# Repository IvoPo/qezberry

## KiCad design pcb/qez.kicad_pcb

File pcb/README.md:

# QEZBerry PCB

### Features

- Powered by an rp2040
- Basic ESD and overvoltage protection
- Centered USB type-C port for a detachable cable
- Multiple layout options (see below)
- Fully programmable using [QMK](https://qmk.fm) and [Vial](https://get.vial.today)

---

### Supported layouts

---

### Preview

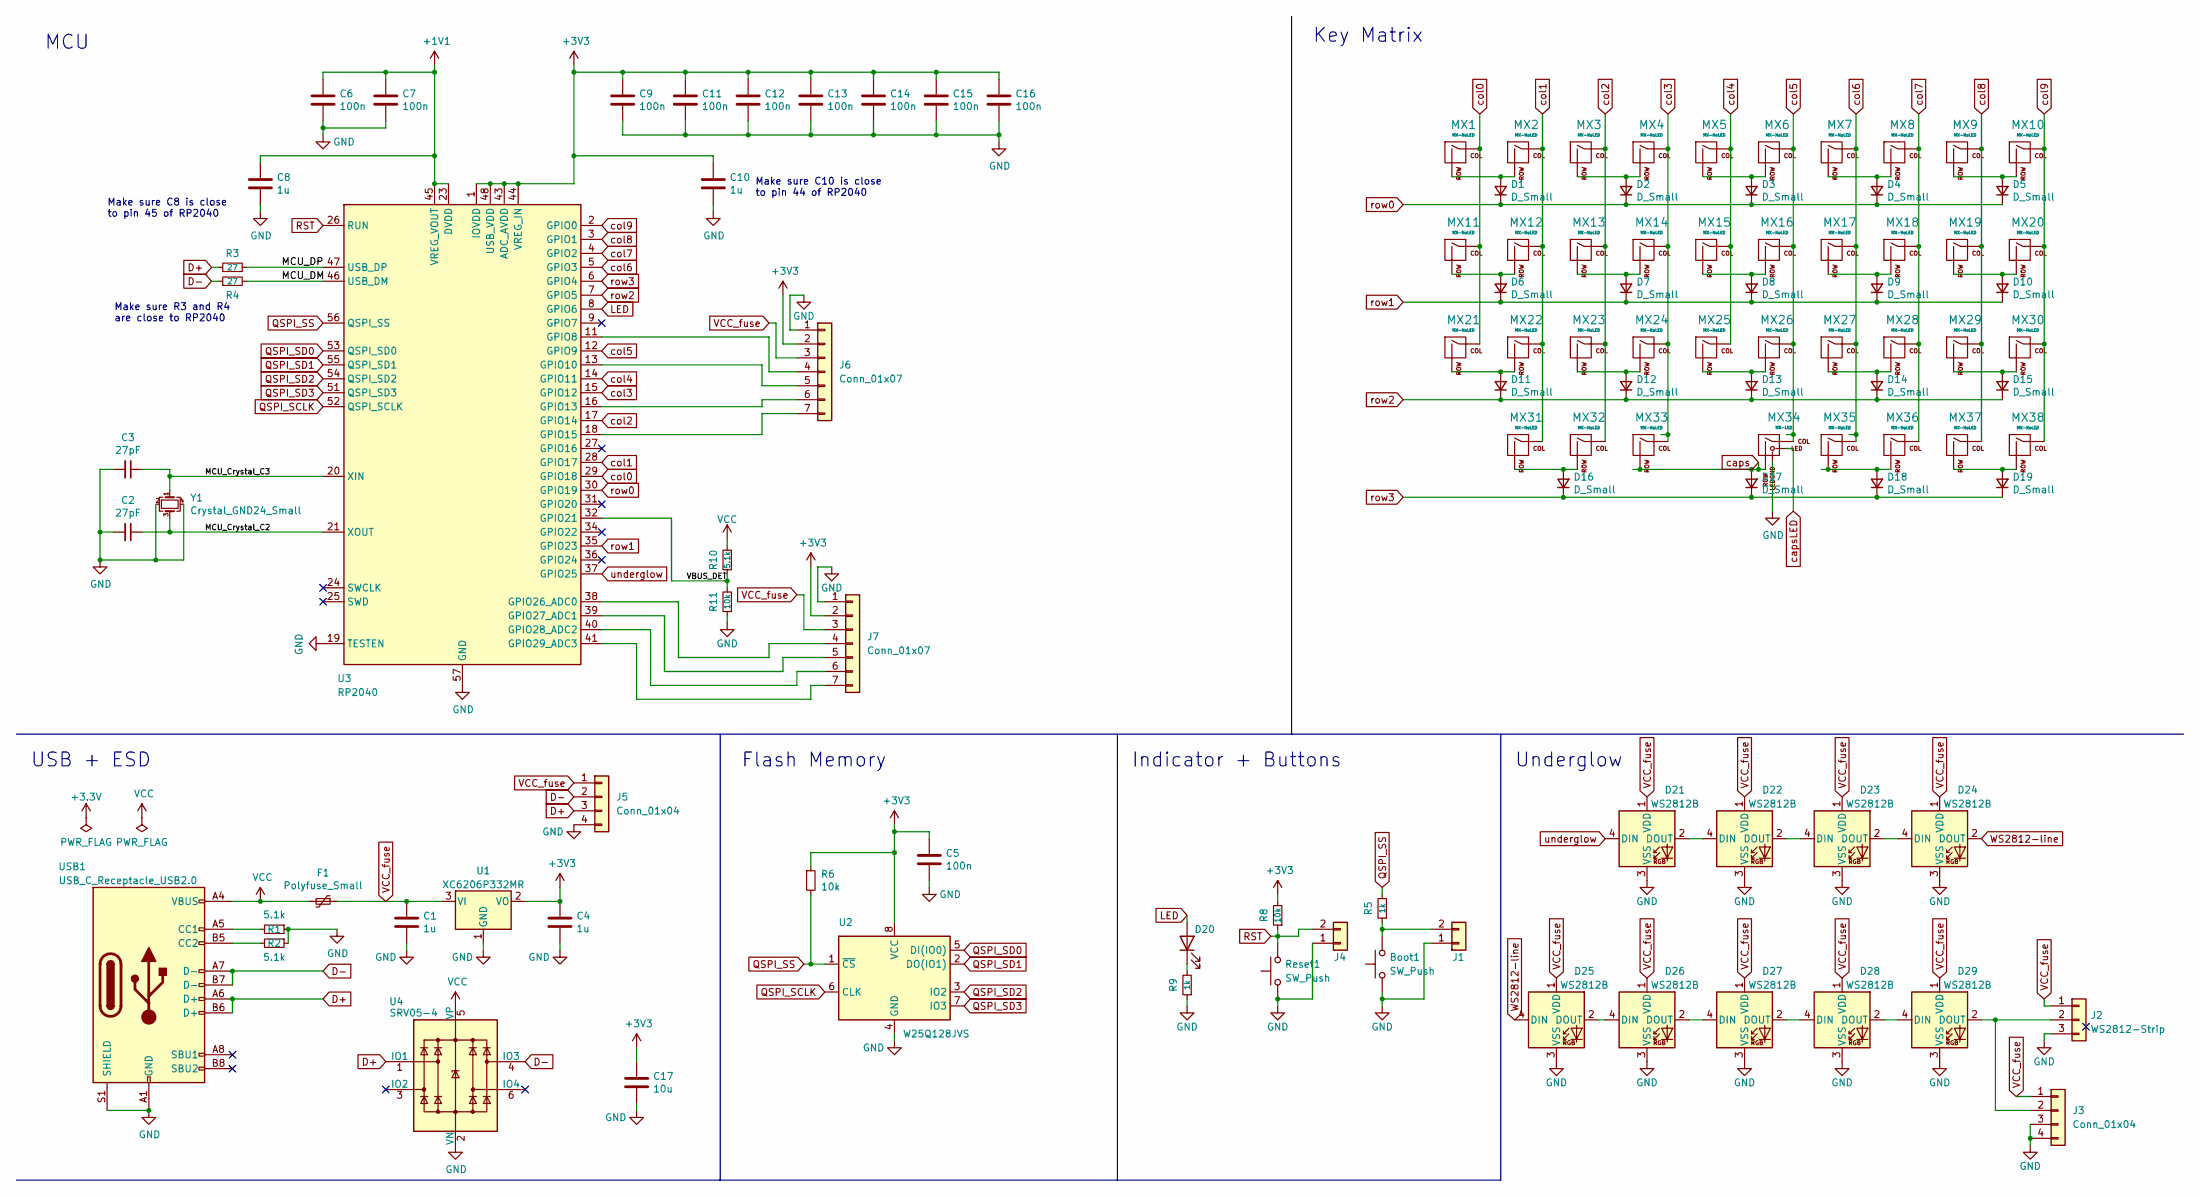
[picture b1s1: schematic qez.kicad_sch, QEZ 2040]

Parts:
Boot1: SW_Push; SW_SPST_SKQG_WithStem; LCSC C319433
C1, C4, C8, C10: 1u; C_0402_1005Metric; LCSC C1523
C2, C3: 27pF; C_0402_1005Metric; LCSC C1557
C5, C6, C7, C9, C11, C12, C13, C14, C15, C16: 100n; C_0402_1005Metric; LCSC C307331
C17: 10u; C_0805_2012Metric; LCSC C1710
D1, D2, D3, D4, D5, D6, D7, D8, D9, D10, D11, D12, D13, D14, D15, D16, D17, D18, D19: D_Small; D_SOT-23_ANK; LCSC C68978
D20: LED; LED_0402_1005Metric; LCSC C130719
D21, D22, D23, D24, D25, D26, D27, D28, D29: WS2812B; LED_WS2812B_PLCC4_5.0x5.0mm_P3.2mm
F1: Polyfuse_Small; Fuse_1206_3216Metric; LCSC C69688
J1, J4: Conn_01x02; PinHeader_1x02_P1.27mm_Vertical
J2: WS2812-Strip; PinHeader_1x03_P1.27mm_Vertical
J3: Conn_01x04; Molex_Pico-EZmate_78171-0004_1x04-1MP_P1.20mm_Vertical
J5: Conn_01x04
J6: Conn_01x07; PinSocket_1x07_P2.00mm_Vertical
J7: Conn_01x07; PinSocket_1x07_P1.27mm_Vertical
MX1, MX2, MX3, MX4, MX5, MX6, MX7, MX8, MX9, MX12, MX13, MX14, MX15, MX16, MX17, MX18, MX19, MX20, MX22, MX23, MX24, MX25, MX26, MX27, MX28, MX29, MX31, MX32, MX36, MX37, MX38: MX-NoLED; MXOnly-1U-NoLED
MX10, MX11: MX-NoLED; MXOnly-1.25U-NoLED
MX21: MX-NoLED; MXOnly-1.75U-NoLED
MX30: MX-NoLED; MXOnly-1.5U-NoLED
MX33: MX-NoLED; MXOnly-2.75U-ReversedStabilizers-NoLED
MX34: MX-LED; MXOnly-1.25U
MX35: MX-NoLED; MXOnly-2.25U-ReversedStabilizers-NoLED
R1, R2: 5.1k; R_0805_2012Metric; LCSC C27834
R3, R4: 27; R_0402_1005Metric; LCSC C17561
R5, R9: 1k; R_0402_1005Metric; LCSC C11702
R6: 10k; R_0805_2012Metric; LCSC C17414
R8, R11: 10k; R_0402_1005Metric; LCSC C25744
R10: 5.1k; R_0402_1005Metric; LCSC C25905
Reset1: SW_Push; SW_SPST_SKQG_WithStem; LCSC C319433
U1: XC6206P332MR; SOT-23; LCSC C5446
U2: W25Q128JVS; SOIC-8_5.23x5.23mm_P1.27mm; LCSC C97521
U3: RP2040; QFN-56-1EP_7x7mm_P0.4mm_EP3.2x3.2mm; LCSC C2040
U4: SRV05-4; SOT-23-6; LCSC C85364
USB1: USB_C_Receptacle_USB2.0; USB_C_Receptacle_HRO_TYPE-C-31-M-12; LCSC C165948
Y1: Crystal_GND24_Small; Crystal_SMD_3225-4Pin_3.2x2.5mm; LCSC C13738

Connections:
+1V1: C6.1, C7.1, C8.1, U3.23 (DVDD), U3.45 (VREG_VOUT), U3.50 (DVDD)
+3V3: C4.1, C5.1, C9.1, C10.1, C11.1, C12.1, C13.1, C14.1, C15.1, C16.1, C17.1, J6.2, J7.2, R6.1, R8.2, U1.2 (VO), U2.8 (VCC), U3.1 (IOVDD), U3.10 (IOVDD), U3.22 (IOVDD), U3.33 (IOVDD), U3.42 (IOVDD), U3.43 (ADC_AVDD), U3.44 (VREG_IN), U3.48 (USB_VDD), U3.49 (IOVDD)
/MCU_Crystal_C2: C2.1, U3.21 (XOUT), Y1.3
/MCU_Crystal_C3: C3.1, U3.20 (XIN), Y1.1
/MCU_DM: R4.2, U3.46 (USB_DM)
/MCU_DP: R3.2, U3.47 (USB_DP)
/VBUS_DET: R10.1, R11.2, U3.32 (GPIO21)
D+: J5.3, R3.1, U4.1 (IO1), USB1.A6 (D+), USB1.B6 (D+)
D-: J5.2, R4.1, U4.4 (IO3), USB1.A7 (D-), USB1.B7 (D-)
GND: Boot1.1, C1.2, C2.2, C3.2, C4.2, C5.2, C6.2, C7.2, C8.2, C9.2, C10.2, C11.2, C12.2, C13.2, C14.2, C15.2, C16.2, C17.2, D21.3 (VSS), D22.3 (VSS), D23.3 (VSS), D24.3 (VSS), D25.3 (VSS), D26.3 (VSS), D27.3 (VSS), D28.3 (VSS), D29.3 (VSS), J1.1, J2.3, J3.3, J3.4, J4.1, J5.4, J6.1, J7.1, MX34.4 (LEDGND), R1.1, R2.1, R9.1, R11.1, Reset1.1, U1.1 (GND), U2.4 (GND), U3.19 (TESTEN), U3.57 (GND), U4.2 (VN), USB1.A1 (GND), USB1.A12 (GND), USB1.B1 (GND), USB1.B12 (GND), USB1.S1 (SHIELD), Y1.2, Y1.4
LED: D20.2 (A), U3.8 (GPIO6)
unnamed: D1.2 (A), MX1.2 (ROW), MX2.2 (ROW)
unnamed: D2.2 (A), MX3.2 (ROW), MX4.2 (ROW)
unnamed: D3.2 (A), MX5.2 (ROW), MX6.2 (ROW)
unnamed: D4.2 (A), MX7.2 (ROW), MX8.2 (ROW)
unnamed: D5.2 (A), MX9.2 (ROW), MX10.2 (ROW)
unnamed: D6.2 (A), MX11.2 (ROW), MX12.2 (ROW)
unnamed: D7.2 (A), MX13.2 (ROW), MX14.2 (ROW)
unnamed: D8.2 (A), MX15.2 (ROW), MX16.2 (ROW)
unnamed: D9.2 (A), MX17.2 (ROW), MX18.2 (ROW)
unnamed: D10.2 (A), MX19.2 (ROW), MX20.2 (ROW)
unnamed: D11.2 (A), MX21.2 (ROW), MX22.2 (ROW)
unnamed: D12.2 (A), MX23.2 (ROW), MX24.2 (ROW)
unnamed: D13.2 (A), MX25.2 (ROW), MX26.2 (ROW)
unnamed: D14.2 (A), MX27.2 (ROW), MX28.2 (ROW)
unnamed: D15.2 (A), MX29.2 (ROW), MX30.2 (ROW)
unnamed: D16.2 (A), MX31.2 (ROW), MX32.2 (ROW)
unnamed 28: D18.2 (A), MX35.2 (ROW), MX36.2 (ROW); also elsewhere on the board
unnamed: D19.2 (A), MX37.2 (ROW), MX38.2 (ROW)
unnamed: D20.1 (K), R9.2
unnamed: D21.2 (DOUT), D22.4 (DIN)
unnamed: D22.2 (DOUT), D23.4 (DIN)
unnamed: D23.2 (DOUT), D24.4 (DIN)
unnamed: D25.2 (DOUT), D26.4 (DIN)
unnamed: D26.2 (DOUT), D27.4 (DIN)
unnamed: D27.2 (DOUT), D28.4 (DIN)
unnamed: D28.2 (DOUT), D29.4 (DIN)
unnamed: D29.2 (DOUT), J2.2, J3.2
unnamed: Boot1.2, J1.2, R5.1
unnamed: J6.4, U3.11 (GPIO8)
unnamed: J6.5, U3.13 (GPIO10)
unnamed: J6.6, U3.16 (GPIO13)
unnamed: J6.7, U3.18 (GPIO15)
unnamed: J7.4, U3.38 (GPIO26_ADC0)
unnamed: J7.5, U3.39 (GPIO27_ADC1)
unnamed: J7.6, U3.40 (GPIO28_ADC2)
unnamed: J7.7, U3.41 (GPIO29_ADC3)
unnamed: R1.2, USB1.A5 (CC1)
unnamed: R2.2, USB1.B5 (CC2)
QSPI_SCLK: U2.6 (CLK), U3.52 (QSPI_SCLK)
QSPI_SD0: U2.5 (DI(IO0)), U3.53 (QSPI_SD0)
QSPI_SD1: U2.2 (DO(IO1)), U3.55 (QSPI_SD1)
QSPI_SD2: U2.3 (IO2), U3.54 (QSPI_SD2)
QSPI_SD3: U2.7 (IO3), U3.51 (QSPI_SD3)
QSPI_SS: R5.2, R6.2, U2.1 (~CS), U3.56 (QSPI_SS)
RST: J4.2, R8.1, Reset1.2, U3.26 (RUN)
VCC: F1.2, R10.2, U4.5 (VP), USB1.A4 (VBUS), USB1.A9 (VBUS), USB1.B4 (VBUS), USB1.B9 (VBUS)
VCC_fuse: C1.1, D21.1 (VDD), D22.1 (VDD), D23.1 (VDD), D24.1 (VDD), D25.1 (VDD), D26.1 (VDD), D27.1 (VDD), D28.1 (VDD), D29.1 (VDD), F1.1, J2.1, J3.1, J5.1, J6.3, J7.3, U1.3 (VI)
WS2812-line: D24.2 (DOUT), D25.4 (DIN)
caps: D17.2 (A), MX33.2 (ROW), MX34.2 (ROW)
col0: MX1.1 (COL), MX11.1 (COL), MX21.1 (COL), U3.29 (GPIO18)
col1: MX2.1 (COL), MX12.1 (COL), MX22.1 (COL), MX31.1 (COL), U3.28 (GPIO17)
col2: MX3.1 (COL), MX13.1 (COL), MX23.1 (COL), MX32.1 (COL), U3.17 (GPIO14)
col3: MX4.1 (COL), MX14.1 (COL), MX24.1 (COL), MX33.1 (COL), U3.15 (GPIO12); also elsewhere on the board
col4: MX5.1 (COL), MX15.1 (COL), MX25.1 (COL), U3.14 (GPIO11)
col5: MX6.1 (COL), MX16.1 (COL), MX26.1 (COL), MX34.1 (COL), U3.12 (GPIO9); also elsewhere on the board
col6: MX7.1 (COL), MX17.1 (COL), MX27.1 (COL), MX35.1 (COL), U3.5 (GPIO3); also elsewhere on the board
col7: MX8.1 (COL), MX18.1 (COL), MX28.1 (COL), MX36.1 (COL), U3.4 (GPIO2)
col8: MX9.1 (COL), MX19.1 (COL), MX29.1 (COL), MX37.1 (COL), U3.3 (GPIO1)
col9: MX10.1 (COL), MX20.1 (COL), MX30.1 (COL), MX38.1 (COL), U3.2 (GPIO0)
row0: D1.1 (K), D2.1 (K), D3.1 (K), D4.1 (K), D5.1 (K), U3.30 (GPIO19)
row1: D6.1 (K), D7.1 (K), D8.1 (K), D9.1 (K), D10.1 (K), U3.35 (GPIO23)
row2: D11.1 (K), D12.1 (K), D13.1 (K), D14.1 (K), D15.1 (K), U3.7 (GPIO5)
row3: D16.1 (K), D17.1 (K), D18.1 (K), D19.1 (K), U3.6 (GPIO4)
underglow: D21.4 (DIN), U3.37 (GPIO25)

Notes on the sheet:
Key Matrix
USB + ESD
Make sure C10 is close to pin 44 of RP2040
Make sure R3 and R4 are close to RP2040
Make sure C8 is close to pin 45 of RP2040
Underglow
MCU
Flash Memory
Indicator + Buttons

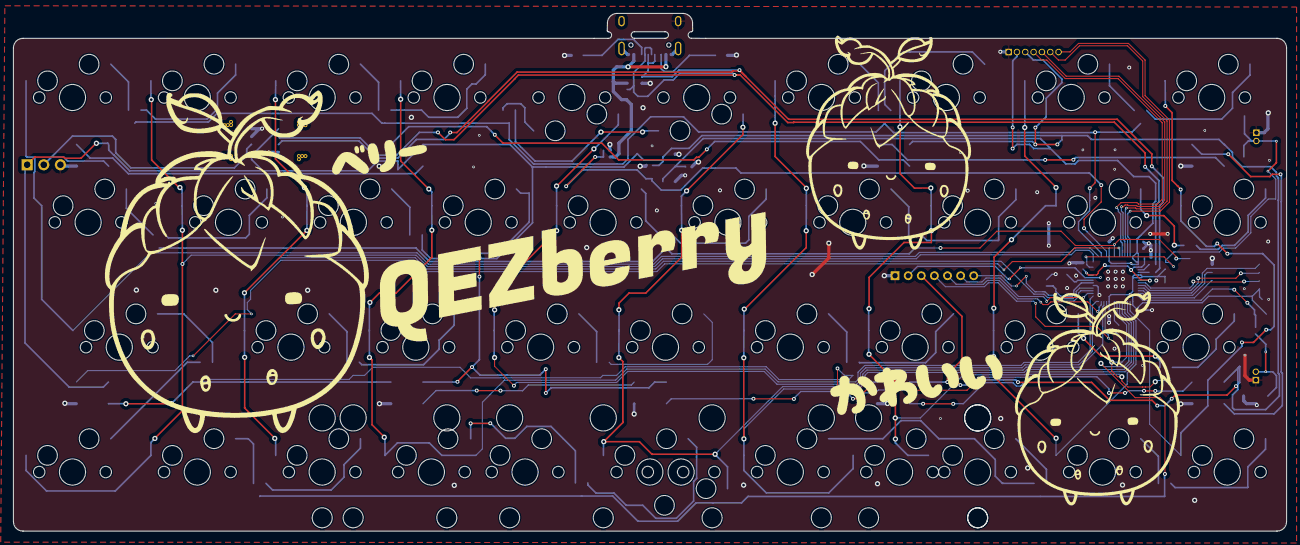
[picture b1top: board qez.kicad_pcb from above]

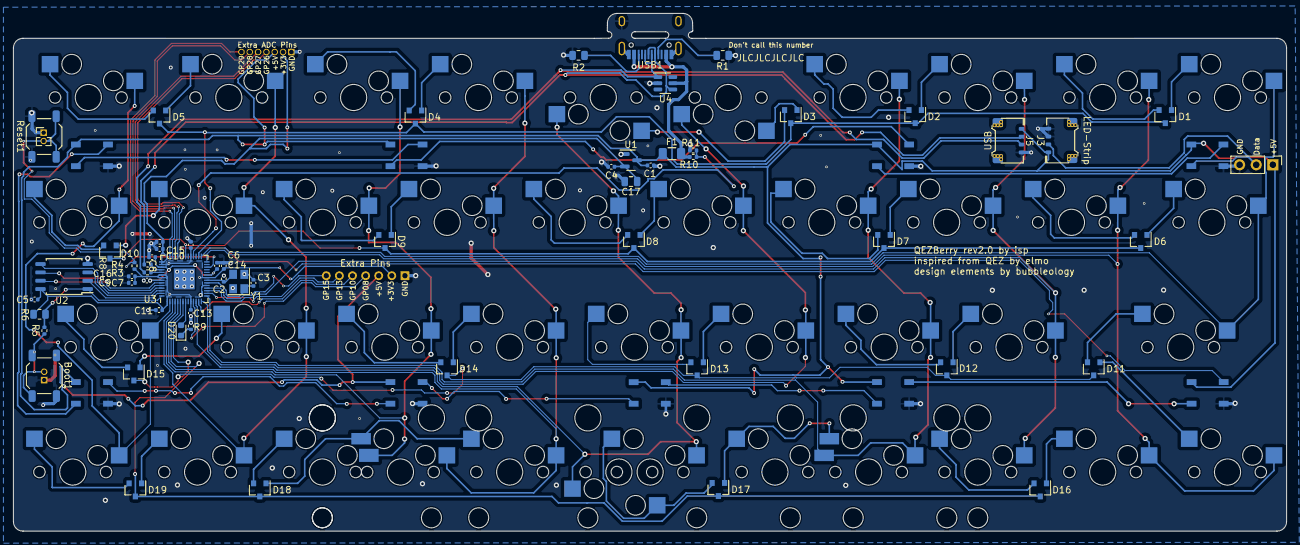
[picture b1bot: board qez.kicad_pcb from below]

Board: 2 copper layers, 194.3 x 79.0 mm, 113 parts (72 on the bottom side), 76 nets.

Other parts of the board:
MX39: MX-NoLED; MXOnly-2.25U-Hotswap-ReversedStabilizers
MX40: MX-NoLED; MXOnly-2U-Hotswap-ReversedStabilizers
MX41: MX-LED; MXOnly-6.25U-Hotswap-ReversedStabilizers-LED

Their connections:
unnamed: MX39.2 (ROW), MX41.2 (ROW)
unnamed 28: MX40.2 (ROW); also elsewhere on the board
col3: MX39.1 (COL); also elsewhere on the board
col5: MX41.1 (COL); also elsewhere on the board
col6: MX40.1 (COL); also elsewhere on the board

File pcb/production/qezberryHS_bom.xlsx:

Comment | Designator | Footprint | JLCPCB Part #（optional）
1u | C1,C4,C8,C10 | C_0402 | C1523
10u | C17 | C_0805 | C1710
27pF | C2,C3 | C_0402 | C1557
100n | C5,C6,C7,C9,C11,C12,C13,C14,C15,C16 | C_0402 | C307331
D_Small | D1,D2,D3,D4,D5,D6,D7,D8,D9,D10,D11,D12,D13,D14,D15,D16,D17,D18,D19 | D_SOT-23-3 | C68978
Polyfuse_Small | F1 | F_1206 | C69688
5.1k | R1,R2 | R_0805 | C27834
5.1k | R10 | R_0402 | C25905
27 | R3,R4 | R_0402 | C25092
1k | R5,R9 | R_0402 | C11702
10k | R6 | R_0805 | C17414
10k | R8,R11 | R_0402 | C25744
SW_Push | Boot,Reset | SW_SPST_CK_RS282G05A3 | C92584
XC6206P332MR | U1 | SOT-23 | C5446
W25Q128JVS | U2 | SOIC-8_5.3x5.3x1.27P | C97521
RP2040 | U3 | LQFN-56_EP_7.0x7.0x0.4P | C2040
SRV05-4 | U4 | SOT-23-6 | C85364
USB_C_Receptacle_USB2.0 | USB1 | TYPE-C-31_L8.94_W7.3 | C165948
Crystal_GND24_Small | Y1 | SMD-CRY-3225_4P | C9002
LED | D20 | LED_0603 | C72041
WS2812B | D21,D22,D23,D24,D25,D26,D27,D28,D29 | LED_WS2812B_PLCC4_5.0x5.0mm_P3.2mm | C2843785
ezmate 4pin | J3,J5 | Molex_Pico-EZmate_78171-0004 | C588524

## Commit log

2022-09-22 init
2023-11-01 initial commit of firmware
2023-11-01 add production and kicad project files
2023-11-01 fix pcb preview pics
2023-11-11 Added Doubleclick Reset for Bootloader Added Compiled Firmware with and without LED-Strip
